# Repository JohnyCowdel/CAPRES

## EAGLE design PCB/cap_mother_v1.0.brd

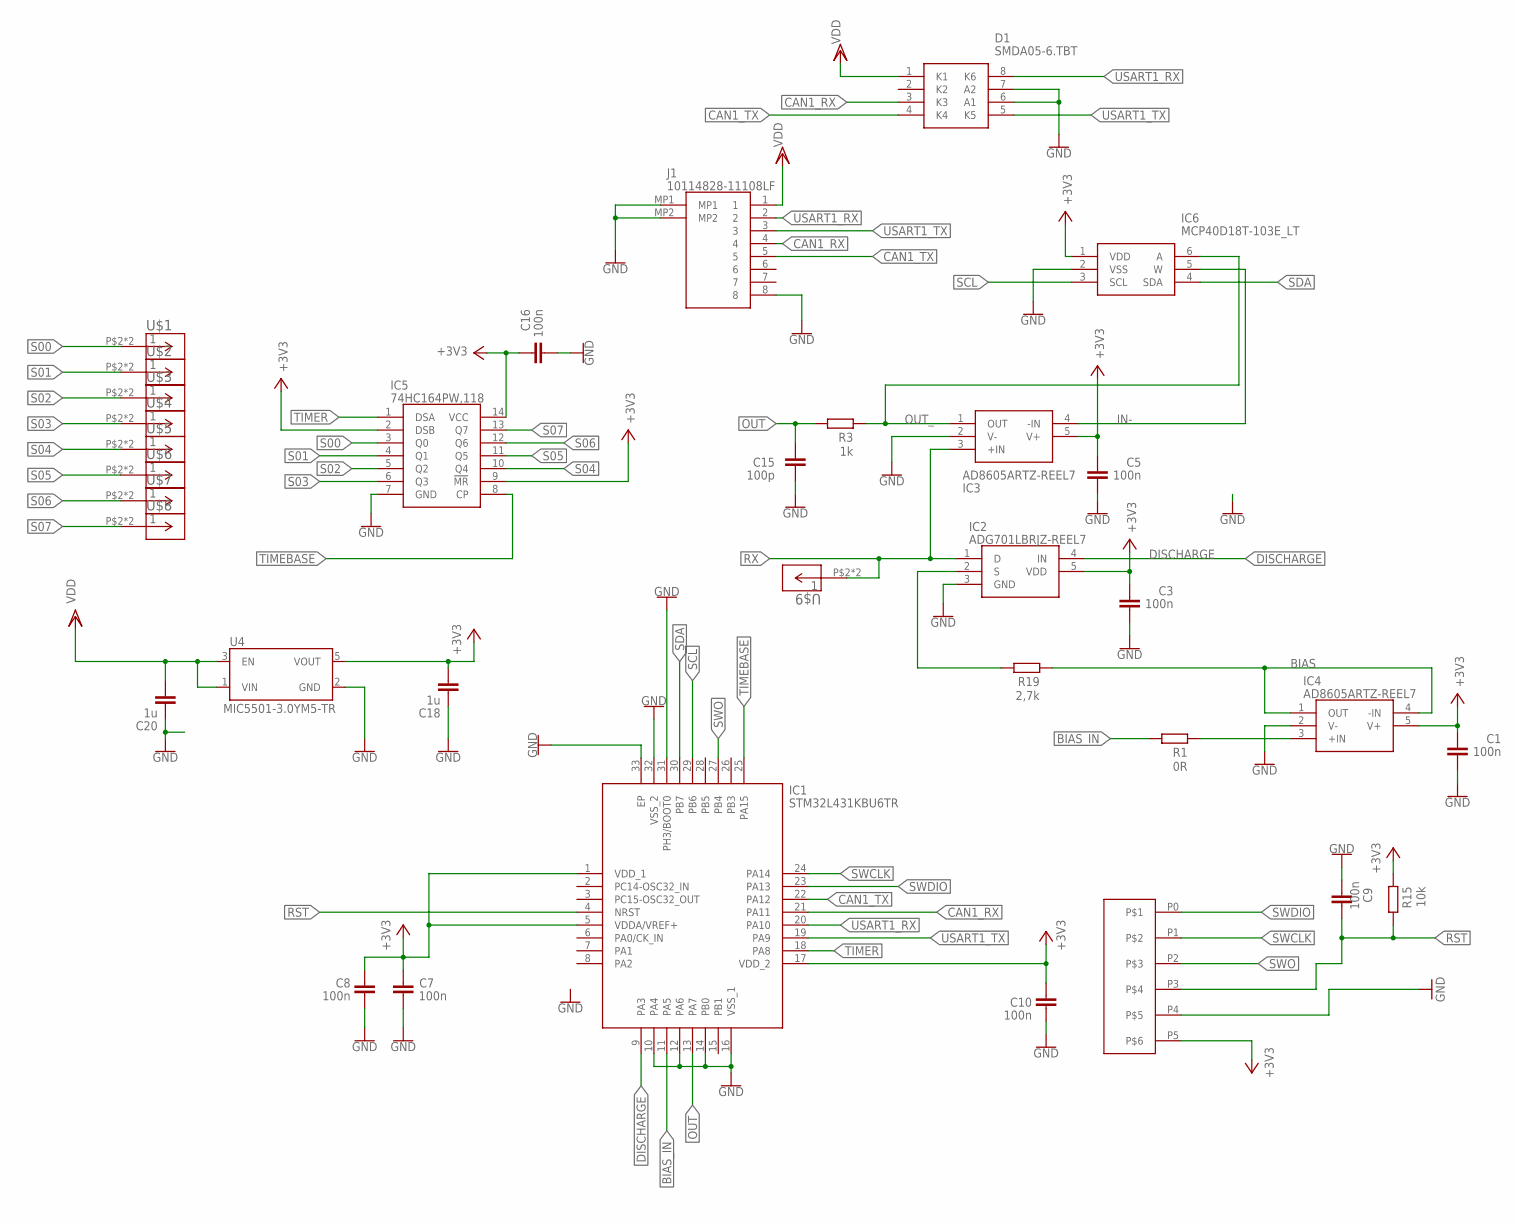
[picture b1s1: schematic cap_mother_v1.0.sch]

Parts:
C1, C3, C5, C7, C8, C10, C16: 100n; C0603K
C9: 100n; C0603
C15: 100p; C0603
C18: 1u; C0603K
C20: 1u; C0603
D1: SMDA05-6.TBT; SOIC127P600X175-8N
IC1: STM32L431KBU6TR; QFN50P500X500X60-33N
IC2: ADG701LBRJZ-REEL7; SOT95P280X145-5N
IC3, IC4: AD8605ARTZ-REEL7; SOT95P280X145-5N
IC5: 74HC164PW,118; SOP65P640X110-14N
IC6: MCP40D18T-103E_LT; SOT65P210X110-6N
J1: 10114828-11108LF; 1011482811108LF
R1: 0R; R0603
R3: 1k; R0603
R15: 10k; R0603
R19: 2,7k; R0603
U4: MIC5501-3.0YM5-TR; SOT95P280X145-5N
U$1, U$2, U$3, U$4, U$5, U$6, U$7, U$8, U$9: CAST_HOLE_1X1SHORT; CASTELATED_HOLE_SHORT
U$10: SMD_SWO; SWD_SMD

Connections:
+3V3: C1.2, C3.2, C5.2, C7.2, C8.2, C10.2, C16.2, C18.2, IC1.1 (VDD_1), IC1.5 (VDDA/VREF+), IC1.17 (VDD_2), IC2.5 (VDD), IC3.5 (V+), IC4.5 (V+), IC5.2 (DSB), IC5.9 (!MR), IC5.14 (VCC), IC6.1 (VDD), R15.1, U4.5 (VOUT), U$10.P5
BIAS: IC4.1 (OUT), IC4.4 (-IN), R19.1
BIAS_IN: IC1.11 (PA5), R1.2
CAN1_RX: D1.3 (K3), IC1.21 (PA11), J1.4
CAN1_TX: D1.4 (K4), IC1.22 (PA12), J1.5
DISCHARGE: IC1.9 (PA3), IC2.4 (IN)
GND: C1.1, C3.1, C5.1, C7.1, C8.1, C9.1, C10.1, C15.1, C16.1, C18.1, C20.1, D1.6 (A1), D1.7 (A2), IC1.10 (PA4), IC1.12 (PA6), IC1.14 (PB0), IC1.16 (VSS_1), IC1.31 (PH3/BOOT0), IC1.32 (VSS_2), IC1.33 (EP), IC2.3 (GND), IC3.2 (V-), IC4.2 (V-), IC5.7 (GND), IC6.2 (VSS), J1.8, J1.MP1, J1.MP2, U4.2 (GND), U$10.P4
IN-: IC3.4 (-IN), IC6.5 (W)
unnamed: IC4.3 (+IN), R1.1
OUT: C15.2, IC1.13 (PA7), R3.2
OUT_: IC3.1 (OUT), IC6.6 (A), R3.1
RST: C9.2, IC1.4 (NRST), R15.2, U$10.P3
RX: IC2.1 (D), IC3.3 (+IN), U$9.P$2, U$9.P$3
S: IC2.2 (S), R19.2
S00: IC5.3 (Q0), U$1.P$2, U$1.P$3
S01: IC5.4 (Q1), U$2.P$2, U$2.P$3
S02: IC5.5 (Q2), U$3.P$2, U$3.P$3
S03: IC5.6 (Q3), U$4.P$2, U$4.P$3
S04: IC5.10 (Q4), U$5.P$2, U$5.P$3
S05: IC5.11 (Q5), U$6.P$2, U$6.P$3
S06: IC5.12 (Q6), U$7.P$2, U$7.P$3
S07: IC5.13 (Q7), U$8.P$2, U$8.P$3
SCL: IC1.29 (PB6), IC6.3 (SCL)
SDA: IC1.30 (PB7), IC6.4 (SDA)
SWCLK: IC1.24 (PA14), U$10.P1
SWDIO: IC1.23 (PA13), U$10.P0
SWO: IC1.27 (PB4), U$10.P2
TIMEBASE: IC1.25 (PA15), IC5.8 (CP)
TIMER: IC1.18 (PA8), IC5.1 (DSA)
USART1_RX: D1.8 (K6), IC1.20 (PA10), J1.2
USART1_TX: D1.5 (K5), IC1.19 (PA9), J1.3
VDD: C20.2, D1.1 (K1), J1.1, U4.1 (VIN), U4.3 (EN)

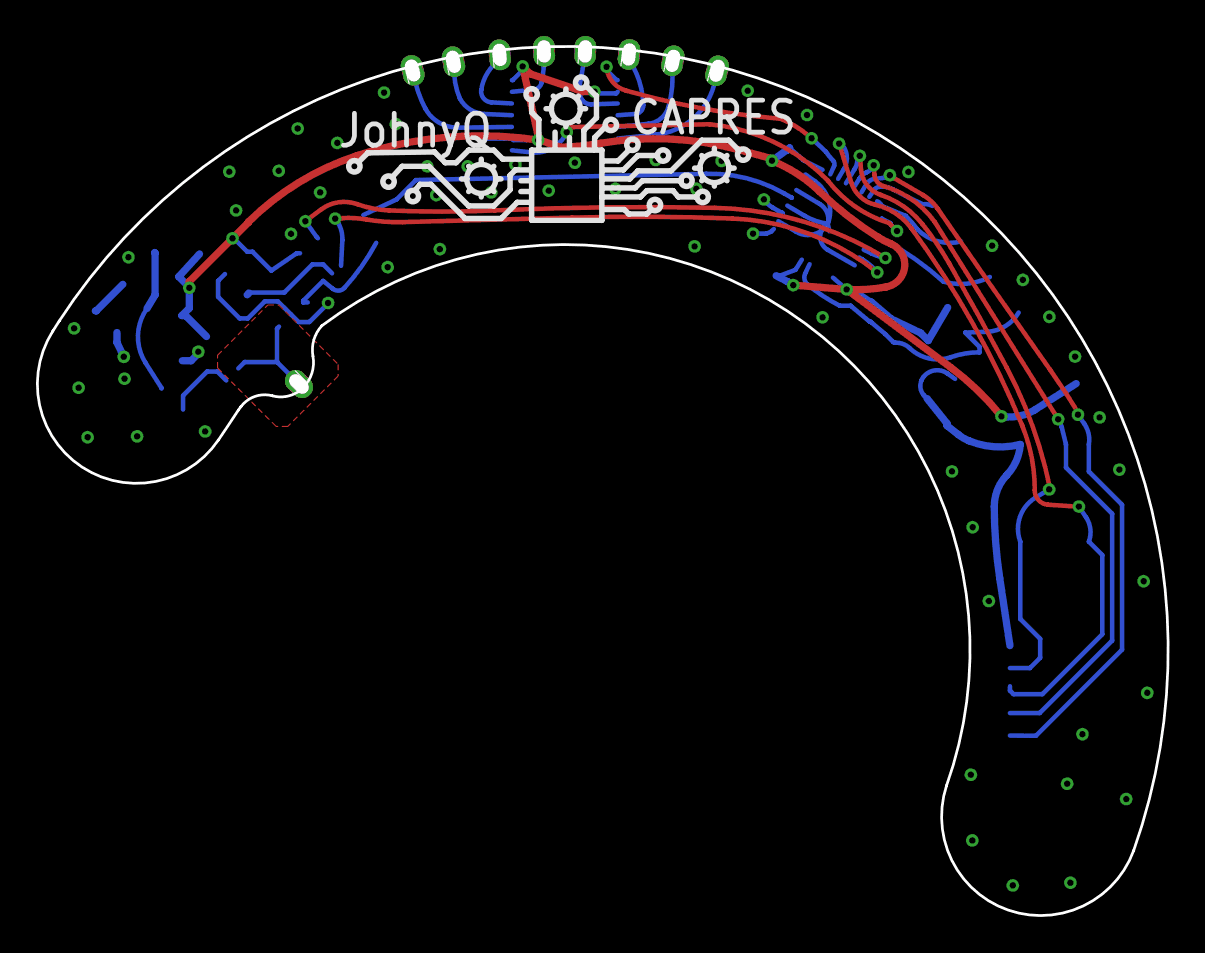
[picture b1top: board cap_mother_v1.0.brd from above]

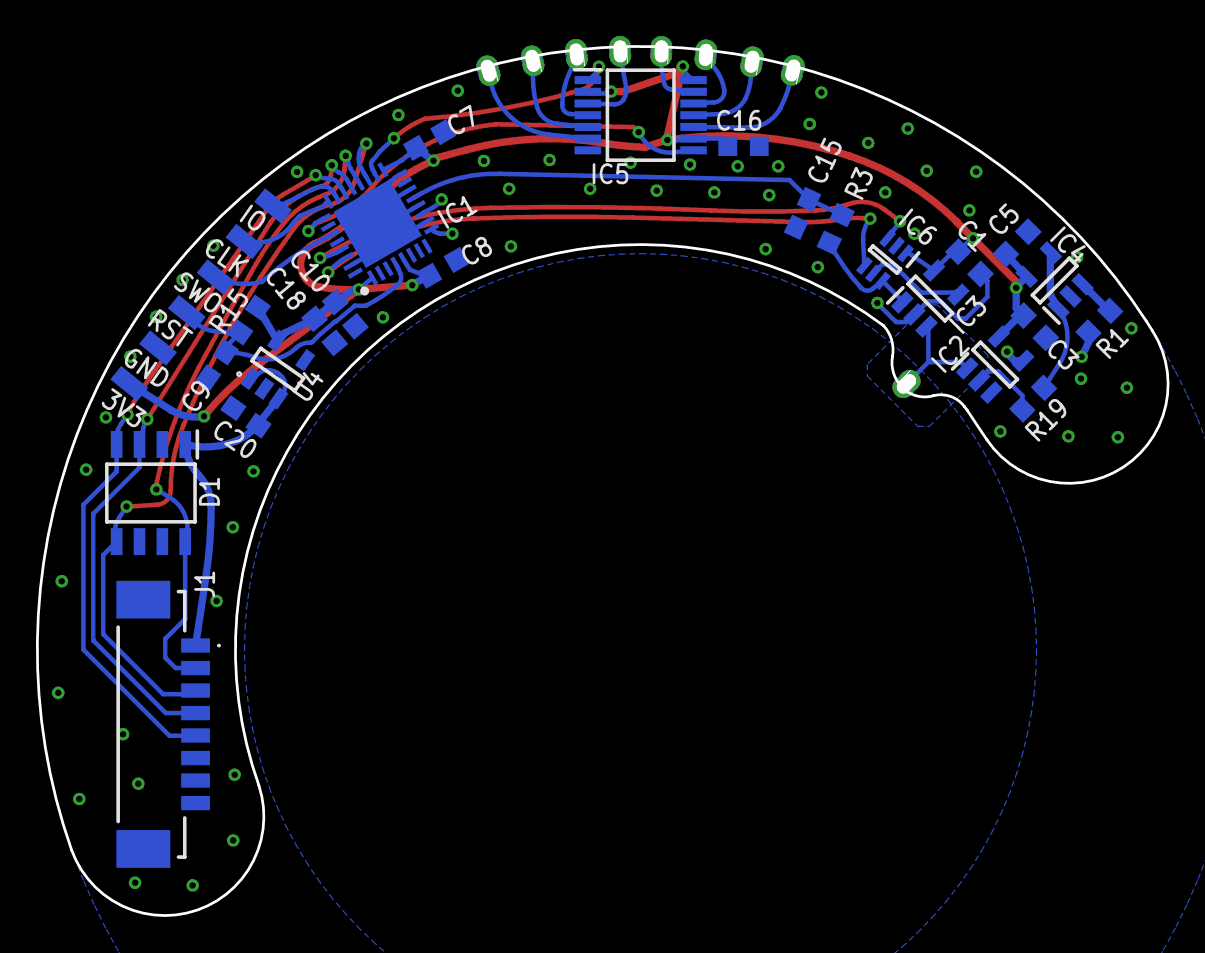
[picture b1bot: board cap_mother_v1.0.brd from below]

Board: 4 copper layers, 62.8 x 48.3 mm, 34 parts (25 on the bottom side), 32 nets.

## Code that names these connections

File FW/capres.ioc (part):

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Mcu.Name=STM32L431K(B-C)Ux
Mcu.Package=UFQFPN32
Mcu.UserName=STM32L431KBUx
PA10.Signal=GPIO_Output
PA11.Mode=CAN_Activate
PA11.Signal=CAN1_RX
PA12.Mode=CAN_Activate
PA12.Signal=CAN1_TX
PA13\ (JTMS-SWDIO).Mode=Trace_Asynchronous_SW
PA13\ (JTMS-SWDIO).Signal=SYS_JTMS-SWDIO
PA14\ (JTCK-SWCLK).Mode=Trace_Asynchronous_SW
PA14\ (JTCK-SWCLK).Signal=SYS_JTCK-SWCLK
PA15\ (JTDI).Signal=S_TIM2_CH1
PA3.Signal=S_TIM15_CH2
PA5.Signal=COMP_DAC12_group
PA7.Signal=ADCx_IN12
PA8.Signal=S_TIM1_CH1
PB3\ (JTDO-TRACESWO).Mode=Trace_Asynchronous_SW
PB3\ (JTDO-TRACESWO).Signal=SYS_JTDO-SWO
PB6.GPIOParameters=GPIO_Speed,GPIO_FM6,GPIO_Pu
PB6.GPIO_FM6=__NULL
PB6.GPIO_Pu=GPIO_PULLUP
PB6.GPIO_Speed=GPIO_SPEED_FREQ_VERY_HIGH
PB6.Mode=I2C
PB6.Signal=I2C1_SCL
PB7.GPIOParameters=GPIO_Speed,GPIO_Pu,GPIO_FM7
PB7.GPIO_FM7=__NULL
PB7.GPIO_Pu=GPIO_NOPULL
PB7.GPIO_Speed=GPIO_SPEED_FREQ_VERY_HIGH
PB7.Mode=I2C
PB7.Signal=I2C1_SDA
RCC.HSE_VALUE=8000000
RCC.SYSCLKFreq_VALUE=80000000
RCC.SYSCLKSource=RCC_SYSCLKSOURCE_PLLCLK
board=custom

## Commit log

2023-10-09 final_version of v1.0 HW
2024-04-08 fw hw setup

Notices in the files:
parts and their libraries:
SparkFun-PowerSymbols: Licensing: Creative Commons ShareAlike 4.0 International - https://creativecommons.org/licenses/by-sa/4.0
